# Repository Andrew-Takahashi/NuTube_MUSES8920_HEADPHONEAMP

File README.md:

# NuTube_MUSES8920_HEADPHONEAMP

## Version 2 updated

Version 1の配線ミスを修正し，オペアンプを両電源化．

ついでにアノード負荷を変更して2.5+-1Vで使えるように調整．

これによりNuTube単体での増幅率は約3.38倍(10.59 dB)に．

さらにオペアンプのバイアス電流をキャンセルするための抵抗用パッドを追加(R7,R11)．

電源回りのEMIフィルタをコモンモードチョークコイル + 貫通コンデンサで強化．

頑張って小型化して100 * 100 mmにした．

まだ動作確認してないので自己責任でどうぞ．

## Version 1

名前の通りNuTubeとMUSES8920を使ったヘッドホンアンプ．
現状ではNuTubeの配線を間違えているので修正予定．
ついでに両電源化してオペアンプ出力カップリングコンデンサをなくす予定．

参考(前段はパクリ)
www.maroon.dti.ne.jp/jyaku9/electronic/electronic5/electronic5-2.html

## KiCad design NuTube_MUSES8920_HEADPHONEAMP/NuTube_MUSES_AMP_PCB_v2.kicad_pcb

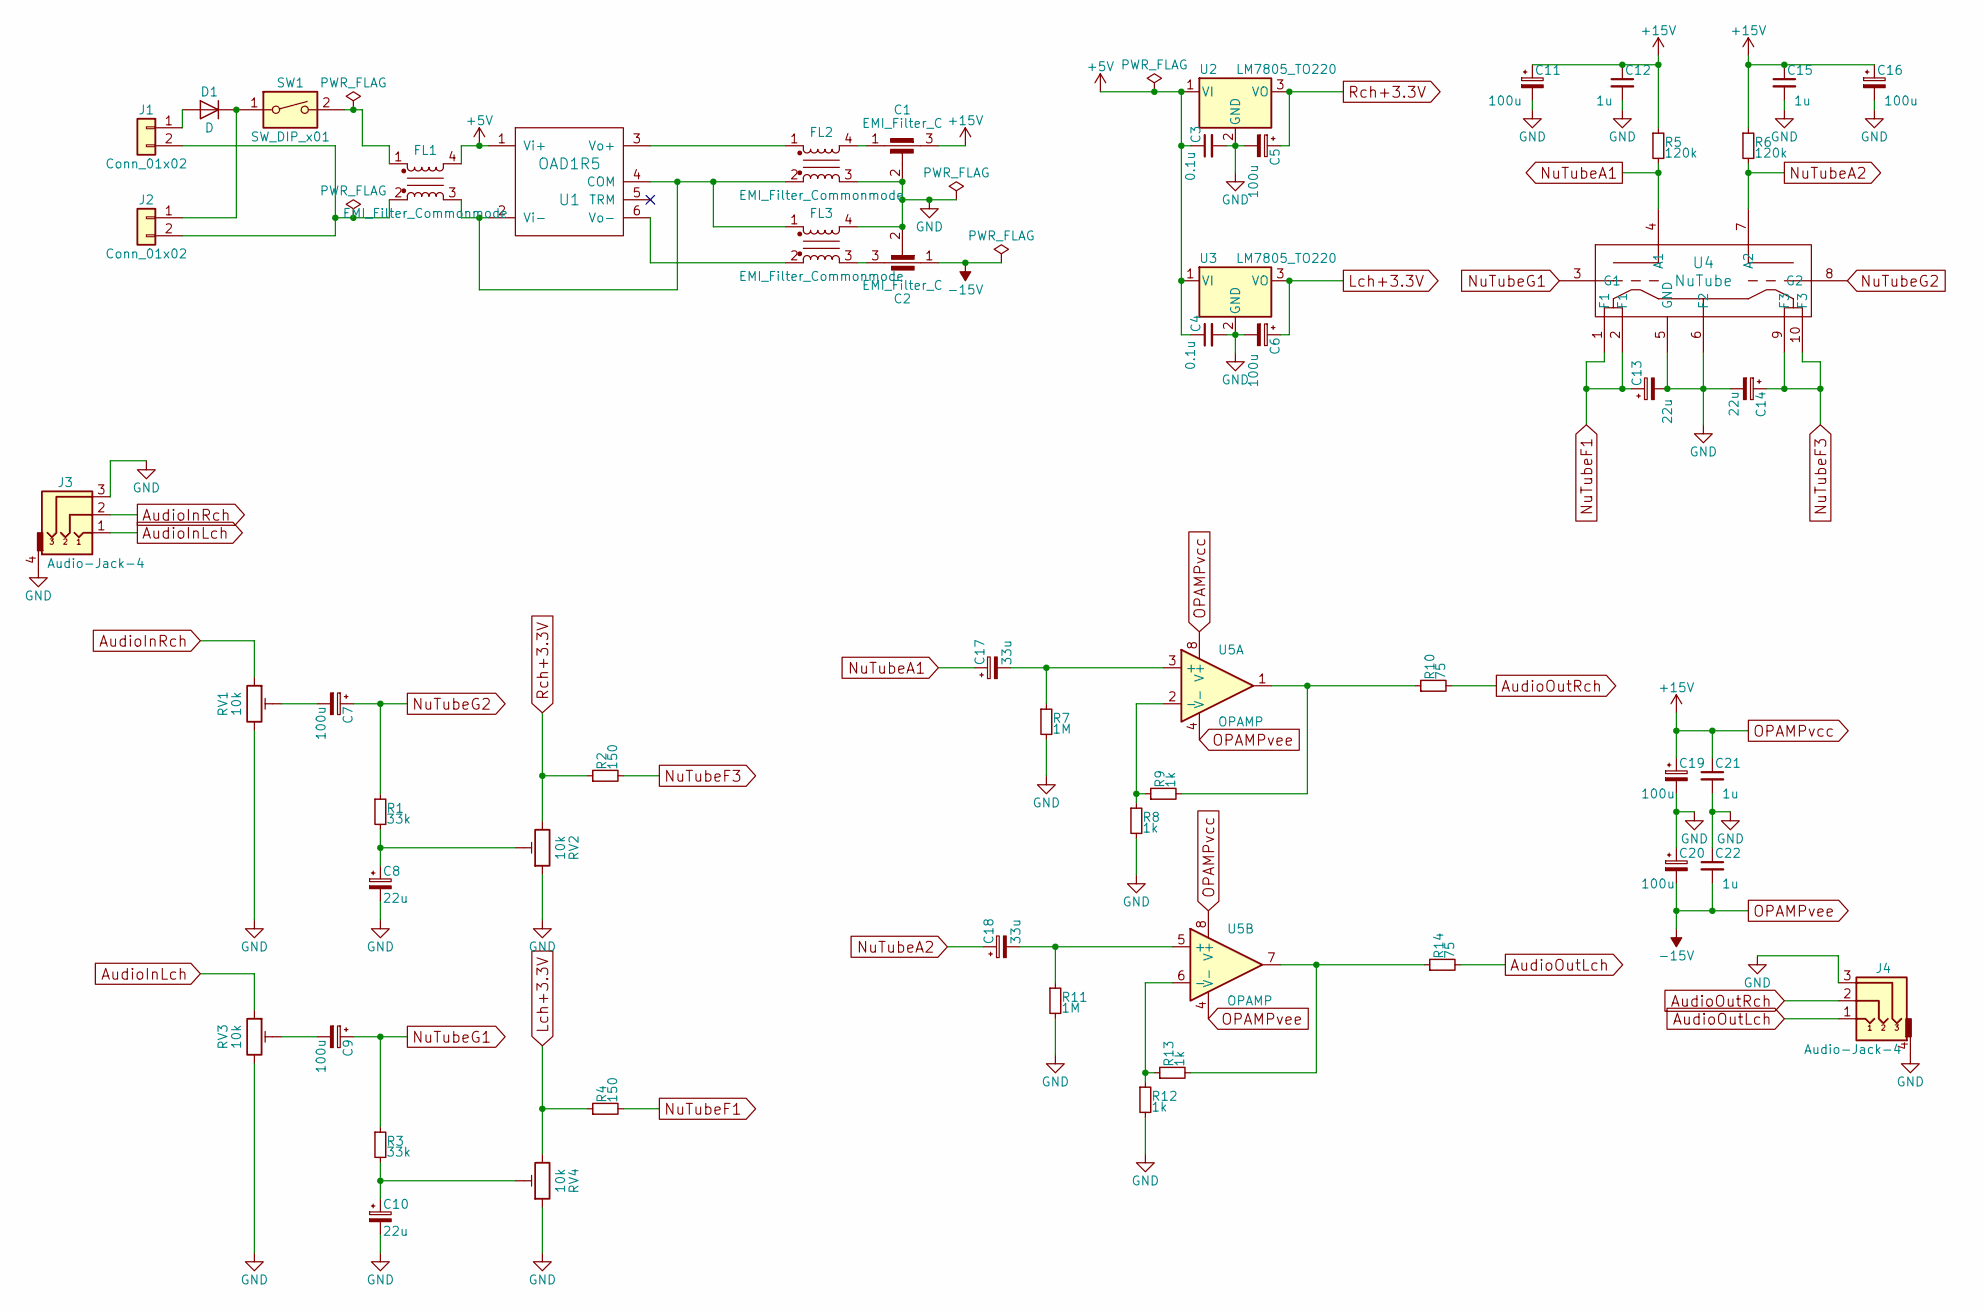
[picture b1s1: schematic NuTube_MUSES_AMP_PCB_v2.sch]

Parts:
C1, C2: EMI_Filter_C; NFM21PC
C3, C4: 0.1u; C_0603_HandSoldering
C5, C6, C11, C16, C19, C20: 100u; CP_Radial_D6.3mm_P2.50mm
C7, C9: 100u; CP_Radial_D10.0mm_P5.00mm
C8, C10, C13, C14: 22u; CP_Radial_D6.3mm_P2.50mm
C12, C15, C21, C22: 1u; ECHU(X)G3
C17, C18: 33u; CP_Radial_D10.0mm_P5.00mm
D1: D; D_DO-41_SOD81_P7.62mm_Horizontal
FL1: EMI_Filter_Commonmode; DLW5BTM
FL2, FL3: EMI_Filter_Commonmode; ACM2520-2P
J1: Conn_01x02; 006P_Holder
J2: Conn_01x02; microUSB(SupplyOnly)
J3, J4: Audio-Jack-4; MJ-4PP-9
R1, R3: 33k; R_0603_HandSoldering
R2, R4: 150; R_0603_HandSoldering
R5, R6: 120k; R_0603_HandSoldering
R7, R11: 1M; R_0603_HandSoldering
R8, R9, R12, R13: 1k; R_0603_HandSoldering
R10, R14: 75; R_0603_HandSoldering
RV1, RV2, RV3, RV4: 10k; LTP3296
SW1: SW_DIP_x01; 2MS6-T1-B3-M1-QE
U1: OAD1R5; OAD1R5-IIOO
U2, U3: LM7805_TO220; SOT-89-3_Handsoldering
U4: NuTube; NuTube_Conversion_Board
U5: OPAMP; DIP-8_W7.62mm_Socket_LongPads

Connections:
+5V: C3.1, C4.1, FL1.4, U1.1 (Vi+), U2.1 (VI), U3.1 (VI)
AudioInLch: J3.1, RV3.1
AudioInRch: J3.2, RV1.1
AudioOutLch: J4.1, R14.2
AudioOutRch: J4.2, R10.2
GND: C1.2, C2.2, C3.2, C4.2, C5.2, C6.2, C8.2, C10.2, C11.2, C12.2, C13.2, C14.2, C15.2, C16.2, C19.2, C20.1, C21.2, C22.1, FL2.3, FL3.4, J3.3, J3.4, J4.3, J4.4, R7.2, R8.2, R11.2, R12.2, RV1.3, RV2.1, RV3.3, RV4.1, U2.2 (GND), U3.2 (GND), U4.5 (GND), U4.6 (F2)
Lch+3.3V: C6.1, R4.1, RV4.3, U3.3 (VO)
unnamed: C1.1, FL2.4
unnamed: C2.3, FL3.3
unnamed: C7.2, RV1.2
unnamed: C8.1, R1.2, RV2.2
unnamed: C9.2, RV3.2
unnamed: C10.1, R3.2, RV4.2
unnamed: C17.2, R7.1, U5.3 (+)
unnamed: C18.2, R11.1, U5.5 (+)
unnamed: D1.1 (K), J2.1, SW1.1
unnamed: D1.2 (A), J1.1
unnamed: FL1.1, SW1.2
unnamed: FL1.2, J1.2, J2.2
unnamed: FL1.3, FL2.2, FL3.1, U1.2 (Vi-), U1.4 (COM)
unnamed: FL2.1, U1.3 (Vo+)
unnamed: FL3.2, U1.6 (Vo-)
unnamed: R8.1, R9.1, U5.2 (-)
unnamed: R9.2, R10.1, U5.1
unnamed: R12.1, R13.1, U5.6 (-)
unnamed: R13.2, R14.1, U5.7
NuTubeA1: C17.1, R5.2, U4.4 (A1)
NuTubeA2: C18.1, R6.2, U4.7 (A2)
NuTubeF1: C13.1, R4.2, U4.1 (F1), U4.2 (F1)
NuTubeF3: C14.1, R2.2, U4.9 (F3), U4.10 (F3)
NuTubeG1: C9.1, R3.1, U4.3 (G1)
NuTubeG2: C7.1, R1.1, U4.8 (G2)
OPAMPvcc: C1.3, C11.1, C12.1, C15.1, C16.1, C19.1, C21.1, R5.1, R6.1, U5.8 (V+)
OPAMPvee: C2.1, C20.2, C22.2, U5.4 (V-)
Rch+3.3V: C5.1, R2.1, RV2.3, U2.3 (VO)

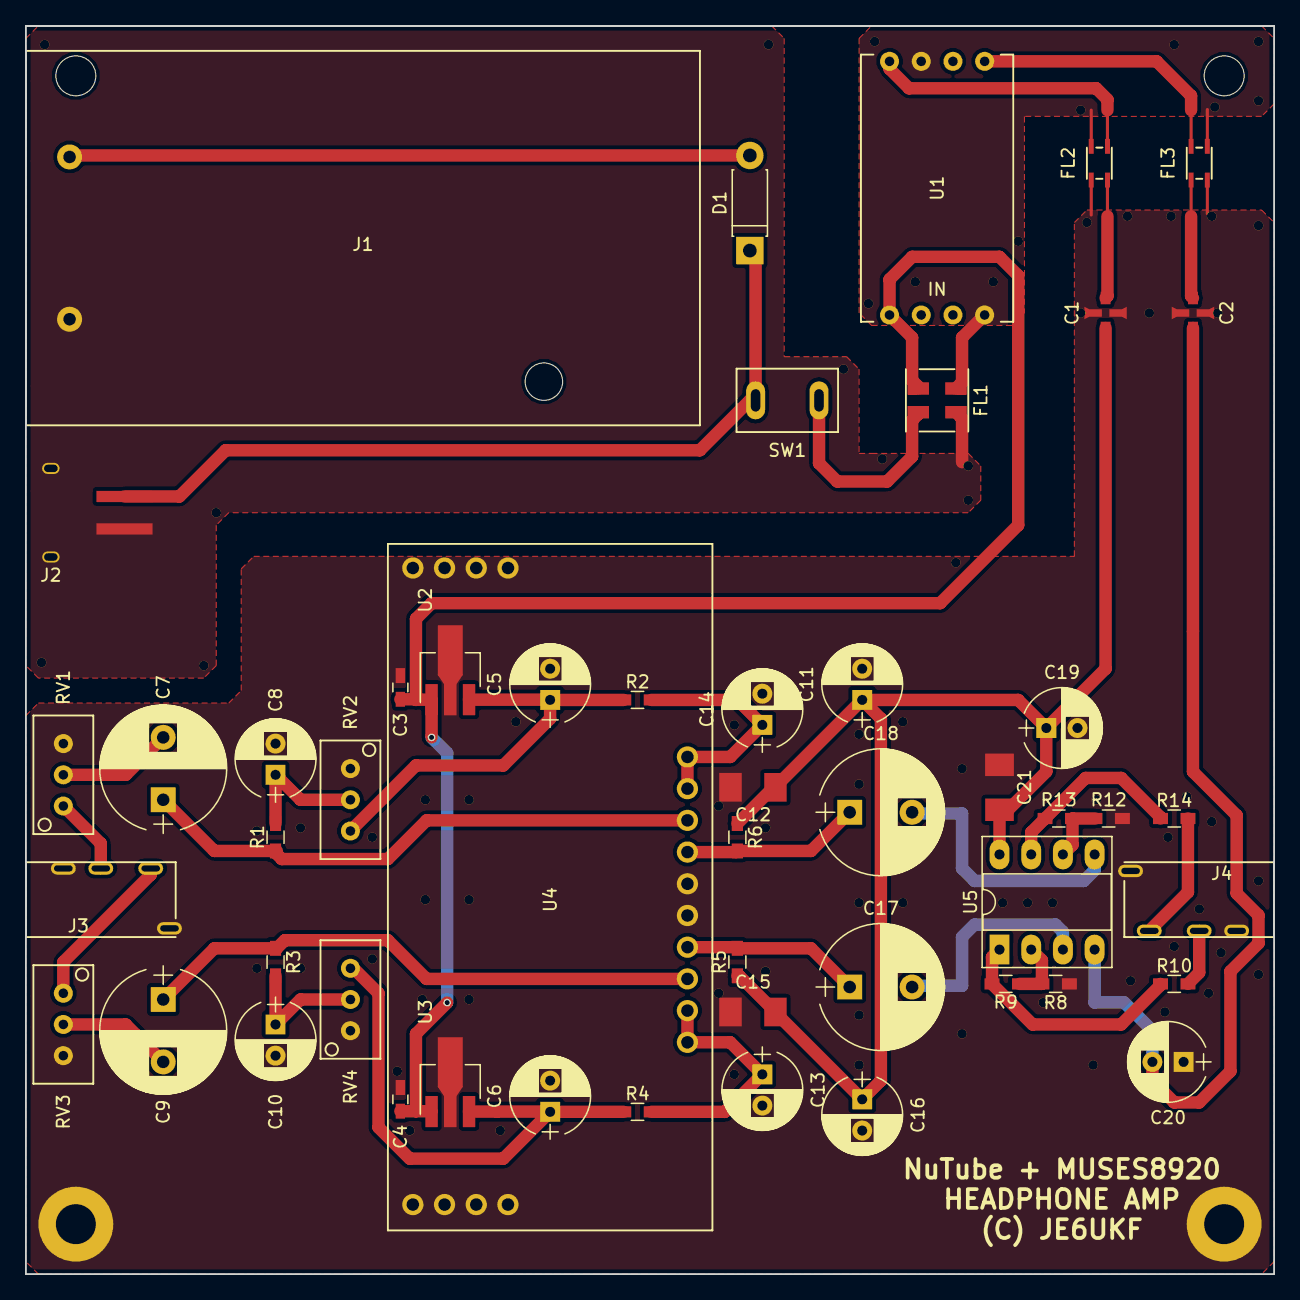
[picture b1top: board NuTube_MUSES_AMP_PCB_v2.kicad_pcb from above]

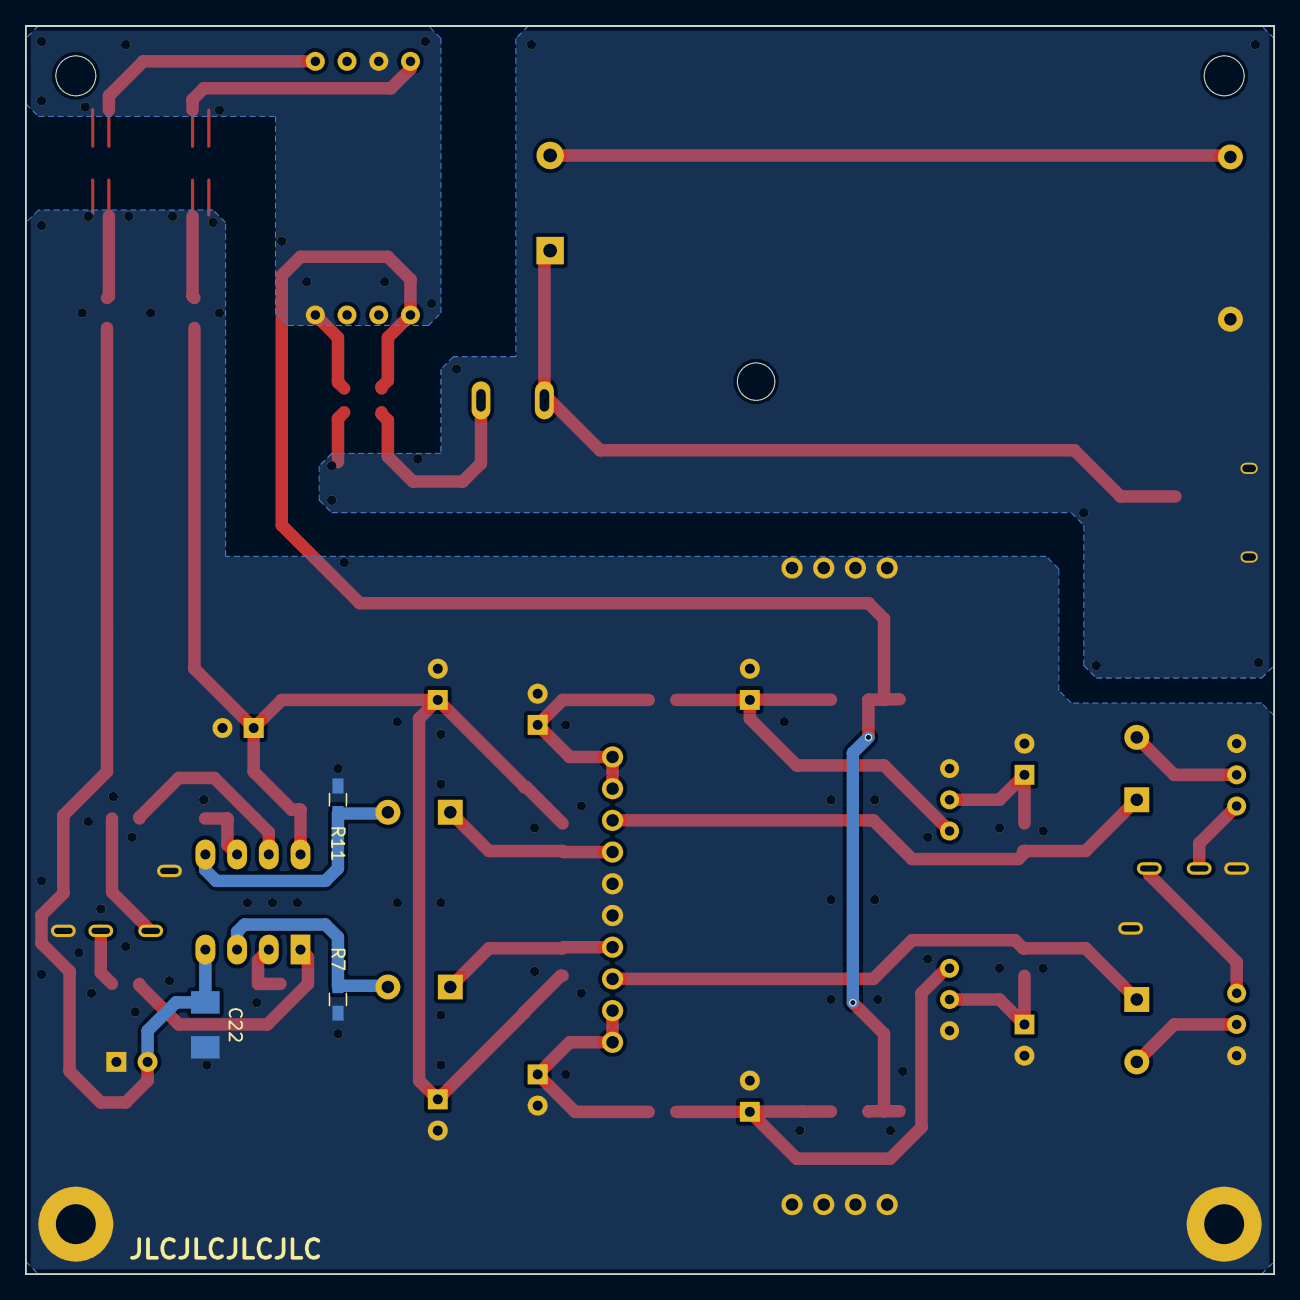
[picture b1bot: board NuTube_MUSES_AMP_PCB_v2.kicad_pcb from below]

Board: 2 copper layers, 100.0 x 100.0 mm, 54 parts (3 on the bottom side), 35 nets.

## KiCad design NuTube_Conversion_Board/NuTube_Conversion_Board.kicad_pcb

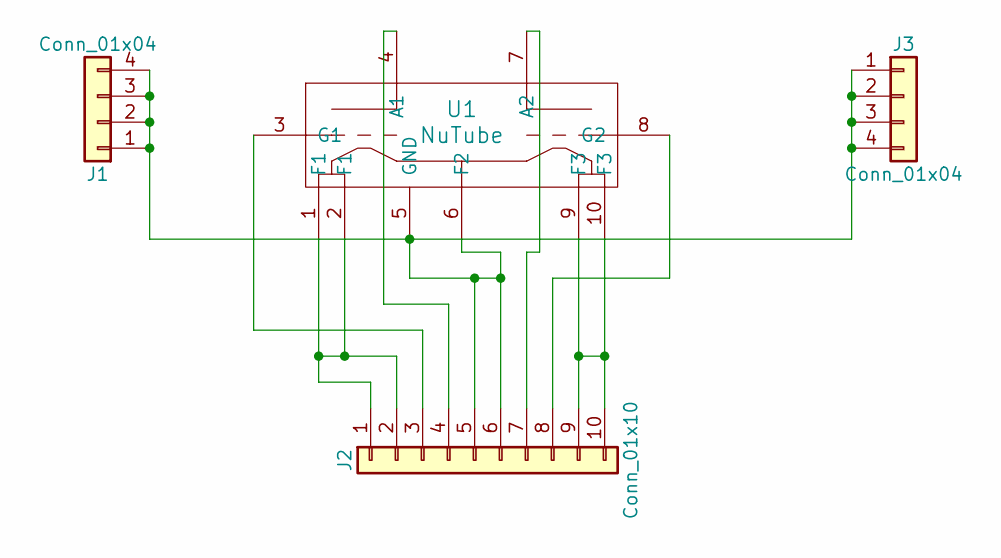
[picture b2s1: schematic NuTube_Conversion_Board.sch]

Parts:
J1, J3: Conn_01x04; Pin_Header_Straight_1x04_Pitch2.54mm
J2: Conn_01x10; Pin_Header_Straight_1x10_Pitch2.54mm
U1: NuTube

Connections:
unnamed: J1.1, J1.2, J1.3, J1.4, J2.5, J2.6, J3.1, J3.2, J3.3, J3.4, U1.5 (GND), U1.6 (F2)
unnamed: J2.1, J2.2, U1.1 (F1), U1.2 (F1)
unnamed: J2.3, U1.3 (G1)
unnamed: J2.4, U1.4 (A1)
unnamed: J2.7, U1.7 (A2)
unnamed: J2.8, U1.8 (G2)
unnamed: J2.9, J2.10, U1.9 (F3), U1.10 (F3)

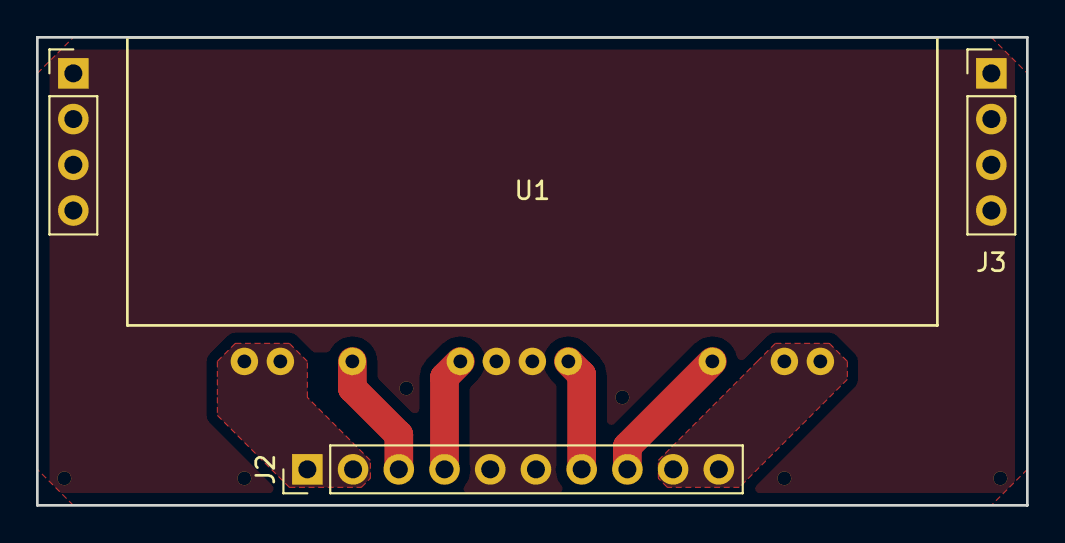
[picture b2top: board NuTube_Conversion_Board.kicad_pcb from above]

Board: 2 copper layers, 55.0 x 26.0 mm, 4 parts (0 on the bottom side), 7 nets.

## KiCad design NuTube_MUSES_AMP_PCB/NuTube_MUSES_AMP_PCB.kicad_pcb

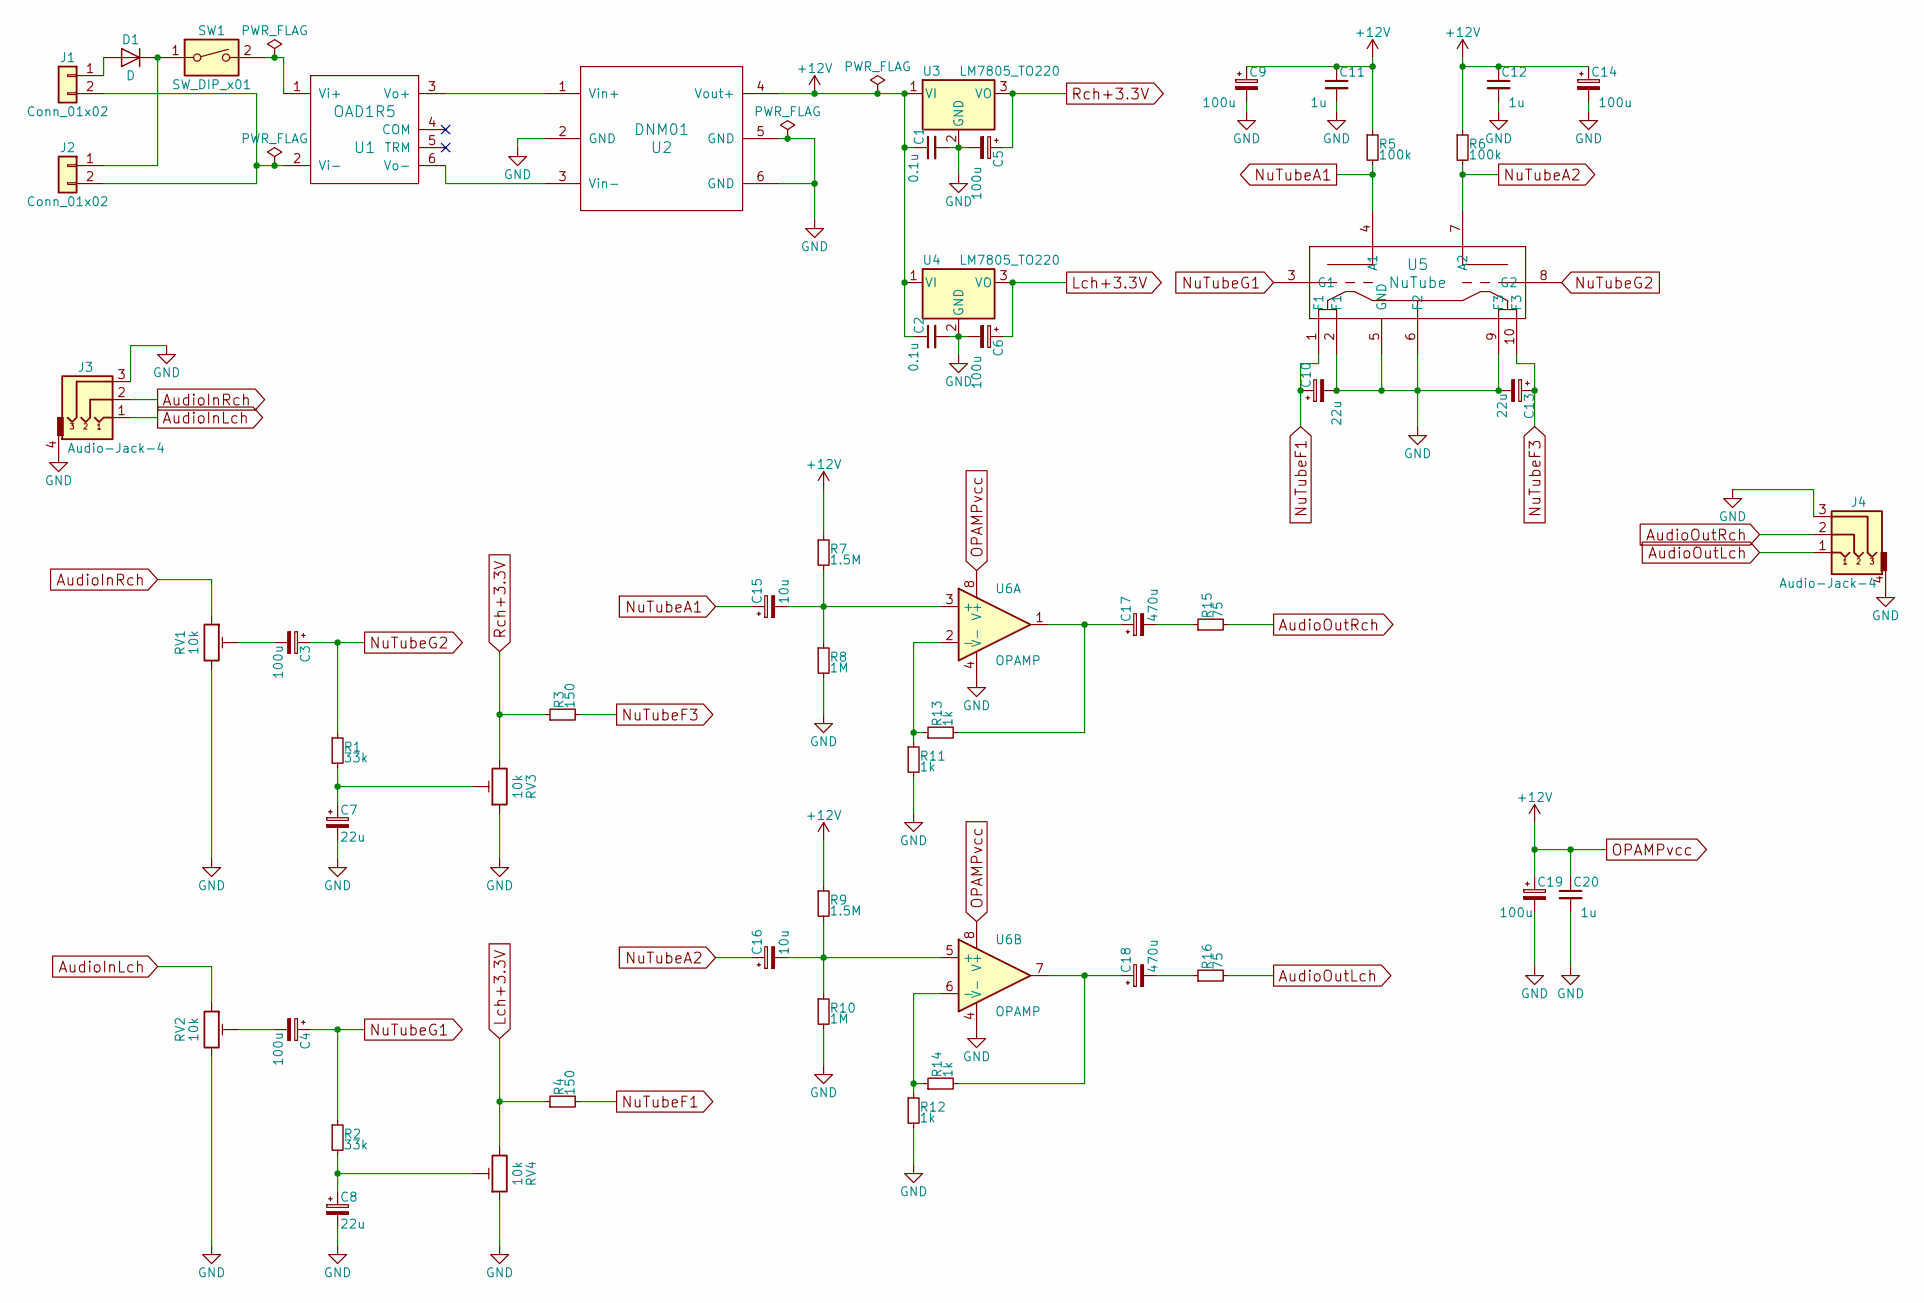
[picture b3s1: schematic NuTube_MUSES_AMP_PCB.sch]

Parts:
C1, C2: 0.1u; C_0603_HandSoldering
C3, C4, C5, C6, C9, C14, C19: 100u; CP_Radial_D6.3mm_P2.50mm
C7, C8, C10, C13: 22u; CP_Radial_D6.3mm_P2.50mm
C11, C12, C20: 1u; C_0603_HandSoldering
C15, C16: 10u; CP_Radial_D5.0mm_P2.50mm
C17, C18: 470u; CP_Radial_D16.0mm_P7.50mm
D1: D; D_DO-41_SOD81_P7.62mm_Horizontal
J1: Conn_01x02; 006P_Holder
J2: Conn_01x02; microUSB(SupplyOnly)
J3, J4: Audio-Jack-4; MJ-4PP-9
R1, R2: 33k; R_Axial_DIN0207_L6.3mm_D2.5mm_P7.62mm_Horizontal
R3, R4: 150; R_Axial_DIN0207_L6.3mm_D2.5mm_P7.62mm_Horizontal
R5, R6: 100k; R_Axial_DIN0207_L6.3mm_D2.5mm_P7.62mm_Horizontal
R7, R9: 1.5M; R_Axial_DIN0207_L6.3mm_D2.5mm_P7.62mm_Horizontal
R8, R10: 1M; R_Axial_DIN0207_L6.3mm_D2.5mm_P7.62mm_Horizontal
R11, R12, R13, R14: 1k; R_Axial_DIN0207_L6.3mm_D2.5mm_P7.62mm_Horizontal
R15, R16: 75; R_Axial_DIN0207_L6.3mm_D2.5mm_P7.62mm_Horizontal
RV1, RV2, RV3, RV4: 10k; LTP3296
SW1: SW_DIP_x01; 2MS6-T1-B3-M1-QE
U1: OAD1R5
U2: DNM01
U3, U4: LM7805_TO220; SOT-223-3_TabPin2
U5: NuTube
U6: OPAMP; DIP-8_W7.62mm_Socket_LongPads

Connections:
AudioInLch: J3.1, RV2.1
AudioInRch: J3.2, RV1.1
AudioOutLch: J4.1, R16.2
AudioOutRch: J4.2, R15.2
GND: C1.2, C2.2, C5.2, C6.2, C7.2, C8.2, C9.2, C10.2, C11.2, C12.2, C13.2, C14.2, C19.2, C20.2, J3.3, J3.4, J4.3, J4.4, R8.2, R10.2, R11.2, R12.2, RV1.3, RV2.3, RV3.1, RV4.1, U2.2 (GND), U2.5 (GND), U2.6 (GND), U3.2 (GND), U4.2 (GND), U5.2 (F1), U5.5 (GND), U5.6 (F2), U5.9 (F3), U6.4 (V-)
Lch+3.3V: C6.1, R4.1, RV4.3, U4.3 (VO)
unnamed: C3.2, RV1.2
unnamed: C4.2, RV2.2
unnamed: C7.1, R1.2, RV3.2
unnamed: C8.1, R2.2, RV4.2
unnamed: C15.2, R7.2, R8.1, U6.3 (+)
unnamed: C16.2, R9.2, R10.1, U6.5 (+)
unnamed: C17.1, R13.2, U6.1
unnamed: C17.2, R15.1
unnamed: C18.1, R14.2, U6.7
unnamed: C18.2, R16.1
unnamed: D1.1 (K), J2.1, SW1.1
unnamed: D1.2 (A), J1.1
unnamed: J1.2, J2.2, U1.2 (Vi-)
unnamed: R11.1, R13.1, U6.2 (-)
unnamed: R12.1, R14.1, U6.6 (-)
unnamed: SW1.2, U1.1 (Vi+)
unnamed: U1.3 (Vo+), U2.1 (Vin+)
unnamed: U1.6 (Vo-), U2.3 (Vin-)
NuTubeA1: C15.1, R5.2, U5.4 (A1)
NuTubeA2: C16.1, R6.2, U5.7 (A2)
NuTubeF1: C10.1, R4.2, U5.1 (F1)
NuTubeF3: C13.1, R3.2, U5.10 (F3)
NuTubeG1: C4.1, R2.1, U5.3 (G1)
NuTubeG2: C3.1, R1.1, U5.8 (G2)
OPAMPvcc: C1.1, C2.1, C9.1, C11.1, C12.1, C14.1, C19.1, C20.1, R5.1, R6.1, R7.1, R9.1, U2.4 (Vout+), U3.1 (VI), U4.1 (VI), U6.8 (V+)
Rch+3.3V: C5.1, R3.1, RV3.3, U3.3 (VO)

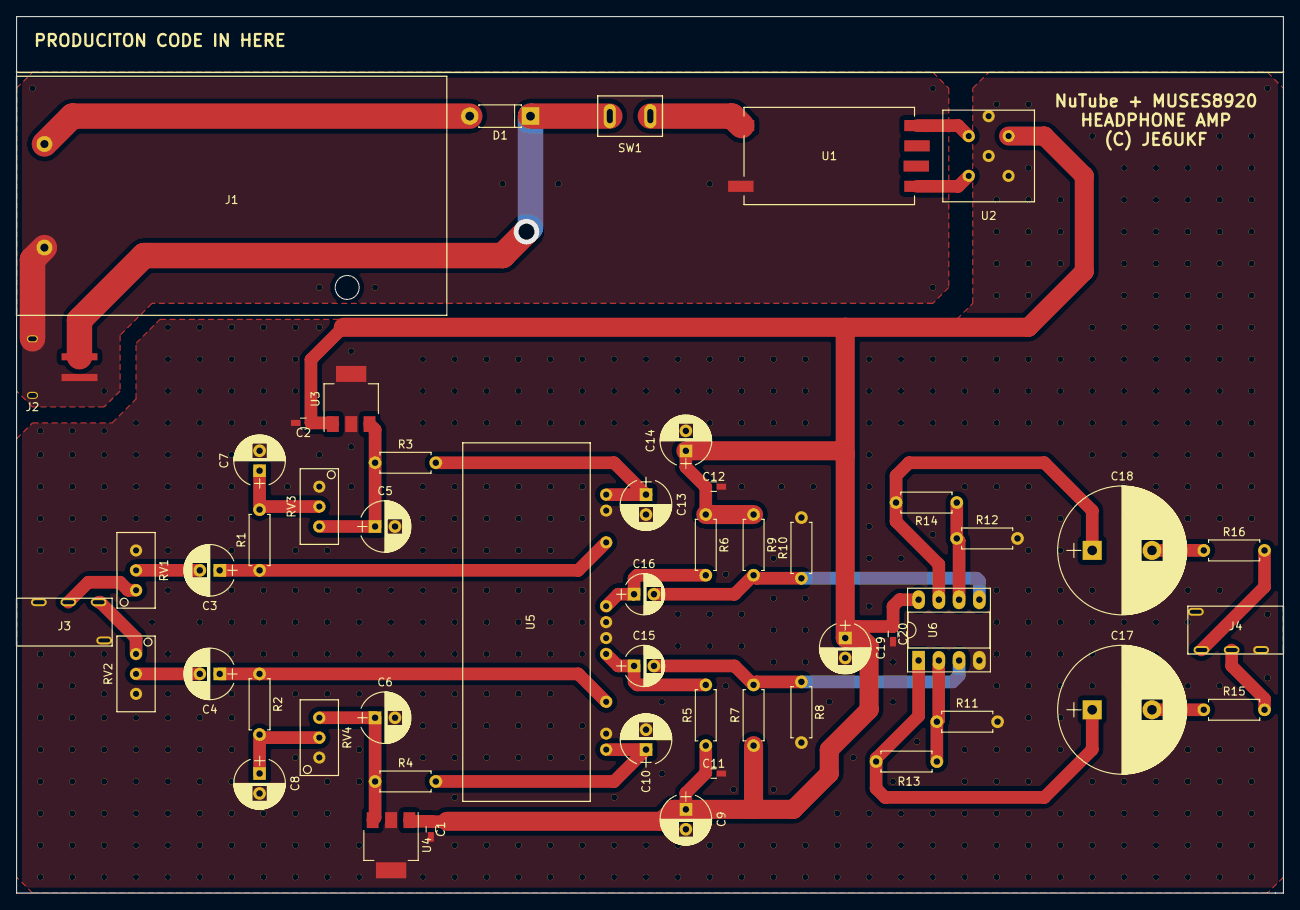
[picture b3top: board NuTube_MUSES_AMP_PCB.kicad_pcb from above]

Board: 2 copper layers, 159.0 x 110.0 mm, 52 parts (0 on the bottom side), 32 nets.

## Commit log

2021-06-19 Made version 2 and Conversion board(NuTube_MUSES8920_HEADPHONEAMP and NuTube_Conversion_Board)
2021-06-19 Add document of selecting anode resistance constant.
